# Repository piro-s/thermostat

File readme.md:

# Thermostat:  
A board for connecting an inductive load (the width of the tracks allows you  
to connect up to 5A); if large currents are required, then a connector is  
provided for connecting control signals of an external relay (Relay Control).  
Scheme was made using the [article](https://habr.com/ru/companies/unwds/articles/390601/).  

### Schemes:  
###### thermostat_v0.1:  
[pdf](docs/thermostat_v0.1.pdf)  

### Images:  
###### thermostat_v0.1:  
top:  
  
bottom:  
  
assembly:  

###### gerber:  
Archive for production:  
[thermostat_v0.1](https://github.com/piro-s/thermostat/raw/main/gerber/thermostat_v0.1.zip)

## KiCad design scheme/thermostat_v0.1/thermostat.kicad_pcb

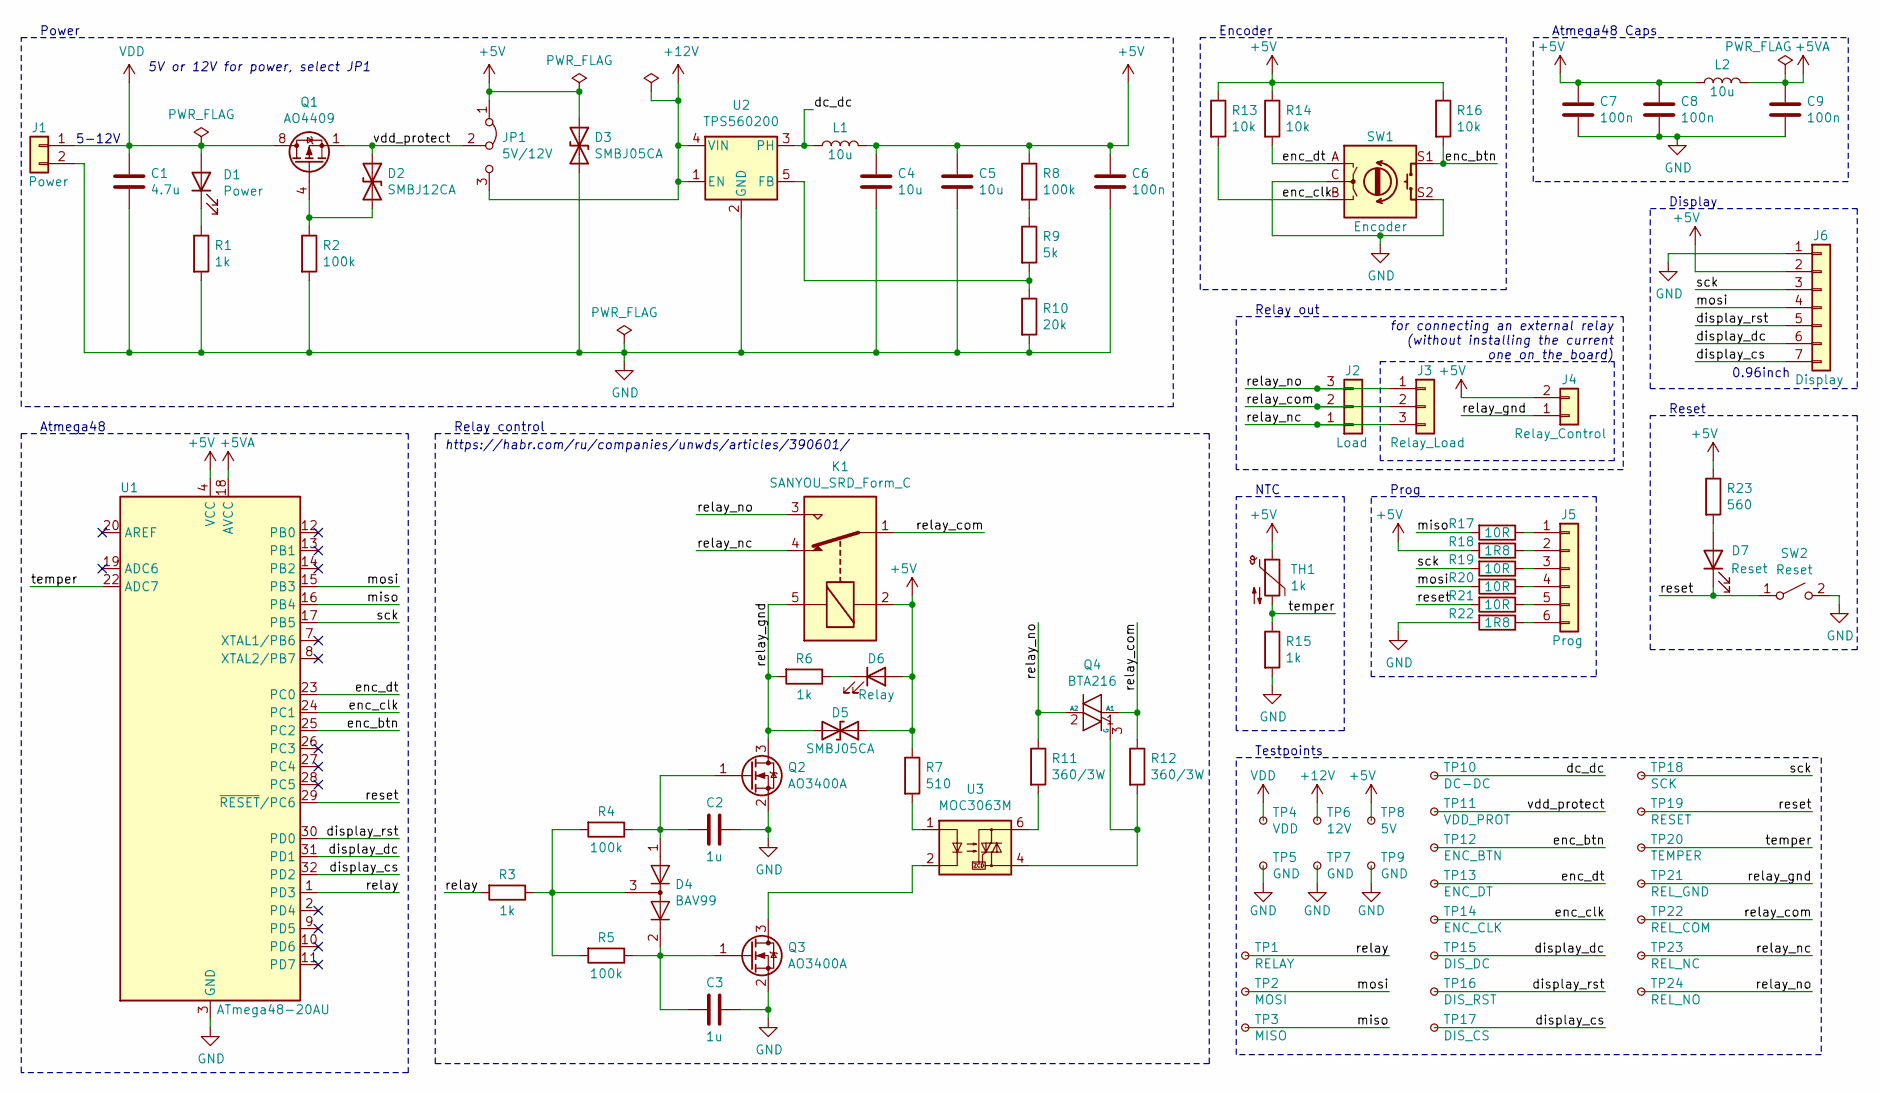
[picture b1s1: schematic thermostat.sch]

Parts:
C1: 4.7u; C_1206_3216Metric_Pad1.33x1.80mm_HandSolder
C2, C3: 1u; C_0603_1608Metric_Pad1.08x0.95mm_HandSolder
C4, C5: 10u; C_1206_3216Metric_Pad1.33x1.80mm_HandSolder
C6, C7, C8, C9: 100n; C_0603_1608Metric_Pad1.08x0.95mm_HandSolder
D1: Power; D_0603_1608Metric_Pad1.05x0.95mm_HandSolder
D2: SMBJ12CA; D_SMA_Handsoldering
D3, D5: SMBJ05CA; D_SMA_Handsoldering
D4: BAV99; SOT-23
D6: Relay; D_0603_1608Metric_Pad1.05x0.95mm_HandSolder
D7: Reset; D_0603_1608Metric_Pad1.05x0.95mm_HandSolder
J1: Power; PhoenixContact_MCV_1,5_2-G-5.08_1x02_P5.08mm_Vertical
J2: Load; PhoenixContact_MCV_1,5_3-G-5.08_1x03_P5.08mm_Vertical
J3: Relay_Load; SolderWire-0.75sqmm_1x03_P4.8mm_D1.25mm_OD2.3mm
J4: Relay_Control; PhoenixContact_MCV_1,5_2-G-5.08_1x02_P5.08mm_Vertical
J5: Prog; IDC-Header_2x03_P2.54mm_Vertical
J6: Display; Display_WAVGAT_0.96
JP1: 5V/12V; PinHeader_1x03_P2.54mm_Vertical
K1: SANYOU_SRD_Form_C; Relay_SPDT_SANYOU_SRD_Series_Form_C
L1, L2: 10u; L_0805_2012Metric_Pad1.15x1.40mm_HandSolder
Q1: AO4409; SOIC-8_3.9x4.9mm_P1.27mm
Q2, Q3: AO3400A; SOT-23
Q4: BTA216; TO-220-3_Vertical
R1, R3, R6, R15: 1k; R_0603_1608Metric_Pad0.98x0.95mm_HandSolder
R2, R4, R5, R8: 100k; R_0603_1608Metric_Pad0.98x0.95mm_HandSolder
R7: 510; R_0603_1608Metric_Pad0.98x0.95mm_HandSolder
R9: 5k; R_0603_1608Metric_Pad0.98x0.95mm_HandSolder
R10: 20k; R_0603_1608Metric_Pad0.98x0.95mm_HandSolder
R11, R12: 360/3W; R_Axial_DIN0617_L17.0mm_D6.0mm_P20.32mm_Horizontal
R13, R14, R16: 10k; R_0603_1608Metric_Pad0.98x0.95mm_HandSolder
R17, R19, R20, R21: 10R; R_0603_1608Metric_Pad0.98x0.95mm_HandSolder
R18, R22: 1R8; R_0603_1608Metric_Pad0.98x0.95mm_HandSolder
R23: 560; R_0603_1608Metric_Pad0.98x0.95mm_HandSolder
SW1: Encoder; RotaryEncoder_Alps_EC11E-Switch_Vertical_H20mm
SW2: Reset; SW_PUSH_6mm
TH1: 1k; PinSocket_1x02_P1.27mm_Vertical
TP1: RELAY; TestPoint_THTPad_D1.0mm_Drill0.5mm
TP2: MOSI; TestPoint_THTPad_D1.0mm_Drill0.5mm
TP3: MISO; TestPoint_THTPad_D1.0mm_Drill0.5mm
TP4: VDD; TestPoint_THTPad_D1.0mm_Drill0.5mm
TP5, TP7, TP9: GND; TestPoint_THTPad_D1.0mm_Drill0.5mm
TP6: 12V; TestPoint_THTPad_D1.0mm_Drill0.5mm
TP8: 5V; TestPoint_THTPad_D1.0mm_Drill0.5mm
TP10: DC-DC; TestPoint_THTPad_D1.0mm_Drill0.5mm
TP11: VDD_PROT; TestPoint_THTPad_D1.0mm_Drill0.5mm
TP12: ENC_BTN; TestPoint_THTPad_D1.0mm_Drill0.5mm
TP13: ENC_DT; TestPoint_THTPad_D1.0mm_Drill0.5mm
TP14: ENC_CLK; TestPoint_THTPad_D1.0mm_Drill0.5mm
TP15: DIS_DC; TestPoint_THTPad_D1.0mm_Drill0.5mm
TP16: DIS_RST; TestPoint_THTPad_D1.0mm_Drill0.5mm
TP17: DIS_CS; TestPoint_THTPad_D1.0mm_Drill0.5mm
TP18: SCK; TestPoint_THTPad_D1.0mm_Drill0.5mm
TP19: RESET; TestPoint_THTPad_D1.0mm_Drill0.5mm
TP20: TEMPER; TestPoint_THTPad_D1.0mm_Drill0.5mm
TP21: REL_GND; TestPoint_THTPad_D1.0mm_Drill0.5mm
TP22: REL_COM; TestPoint_THTPad_D1.0mm_Drill0.5mm
TP23: REL_NC; TestPoint_THTPad_D1.0mm_Drill0.5mm
TP24: REL_NO; TestPoint_THTPad_D1.0mm_Drill0.5mm
U1: ATmega48-20AU; TQFP-32_7x7mm_P0.8mm
U2: TPS560200; SOT-23-5
U3: MOC3063M; DIP-6_W7.62mm

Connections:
+5V: C4.1, C5.1, C6.1, C7.1, C8.1, D3.1 (A1), D5.1 (A1), D6.2 (A), J4.2, J6.2, JP1.1 (A), K1.2, L1.2, L2.1, R7.1, R8.1, R13.1, R14.1, R16.1, R18.2, R23.1, TH1.1, TP8.1, U1.4 (VCC), U1.6 (VCC)
+5VA: C9.1, L2.2, U1.18 (AVCC)
+12V: JP1.3 (B), TP6.1, U2.1 (EN), U2.4 (VIN)
/dc_dc: L1.1, TP10.1, U2.3 (PH)
/display_cs: J6.7, TP17.1, U1.32 (PD2)
/display_dc: J6.6, TP15.1, U1.31 (PD1)
/display_rst: J6.5, TP16.1, U1.30 (PD0)
/enc_btn: R16.2, SW1.S1, TP12.1, U1.25 (PC2)
/enc_clk: R13.2, SW1.B, TP14.1, U1.24 (PC1)
/enc_dt: R14.2, SW1.A, TP13.1, U1.23 (PC0)
/miso: R17.2, TP3.1, U1.16 (PB4)
/mosi: J6.4, R20.2, TP2.1, U1.15 (PB3)
/relay: R3.2, TP1.1, U1.1 (PD3)
/relay_com: J2.2, J3.2, K1.1, Q4.1 (A1), R12.1, TP22.1
/relay_gnd: D5.2 (A2), J4.1, K1.5, Q2.3 (D), R6.2, TP21.1
/relay_nc: J2.1, J3.3, K1.4, TP23.1
/relay_no: J2.3, J3.1, K1.3, Q4.2 (A2), R11.1, TP24.1
/reset: D7.1 (K), R21.2, SW2.1 (A), TP19.1, U1.29 (~RESET~/PC6)
/sck: J6.3, R19.2, TP18.1, U1.17 (PB5)
/temper: R15.1, TH1.2, TP20.1, U1.22 (ADC7)
/vdd_protect: D2.1 (A1), JP1.2 (C), Q1.1 (S), Q1.2 (S), Q1.3 (S), TP11.1
GND: C1.2, C2.1, C3.1, C4.2, C5.2, C6.2, C7.2, C8.2, C9.2, D3.2 (A2), J1.2, J6.1, Q2.2 (S), Q3.2 (S), R1.2, R2.2, R10.2, R15.2, R22.2, SW1.C, SW1.S2, SW2.2 (B), TP5.1, TP7.1, TP9.1, U1.3 (GND), U1.5 (GND), U1.21 (GND), U2.2 (GND)
unnamed: C2.2, D4.1 (K), Q2.1 (G), R4.1
unnamed: C3.2, D4.2 (A), Q3.1 (G), R5.1
unnamed: D1.1 (K), R1.1
unnamed: D2.2 (A2), Q1.4 (G), R2.1
unnamed: D4.3 (K), R3.1, R4.2, R5.2
unnamed: D6.1 (K), R6.1
unnamed: D7.2 (A), R23.2
unnamed: J5.1, R17.1
unnamed: J5.2, R18.1
unnamed: J5.3, R19.1
unnamed: J5.4, R20.1
unnamed: J5.5, R21.1
unnamed: J5.6, R22.1
unnamed: Q3.3 (D), U3.2
unnamed: Q4.3 (G), R12.2, U3.4
unnamed: R7.2, U3.1
unnamed: R8.2, R9.1
unnamed: R9.2, R10.1, U2.5 (FB)
unnamed: R11.2, U3.6
VDD: C1.1, D1.2 (A), J1.1, Q1.5 (D), Q1.6 (D), Q1.7 (D), Q1.8 (D), TP4.1

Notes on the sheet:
Power
Atmega48 Caps
NTC
Encoder
for connecting an external relay (without installing the current one on the board)
Relay out
Relay control
https://habr.com/ru/companies/unwds/articles/390601/
5-12V
Reset
Prog
0.96inch
Display
Atmega48
Testpoints
5V or 12V for power, select JP1

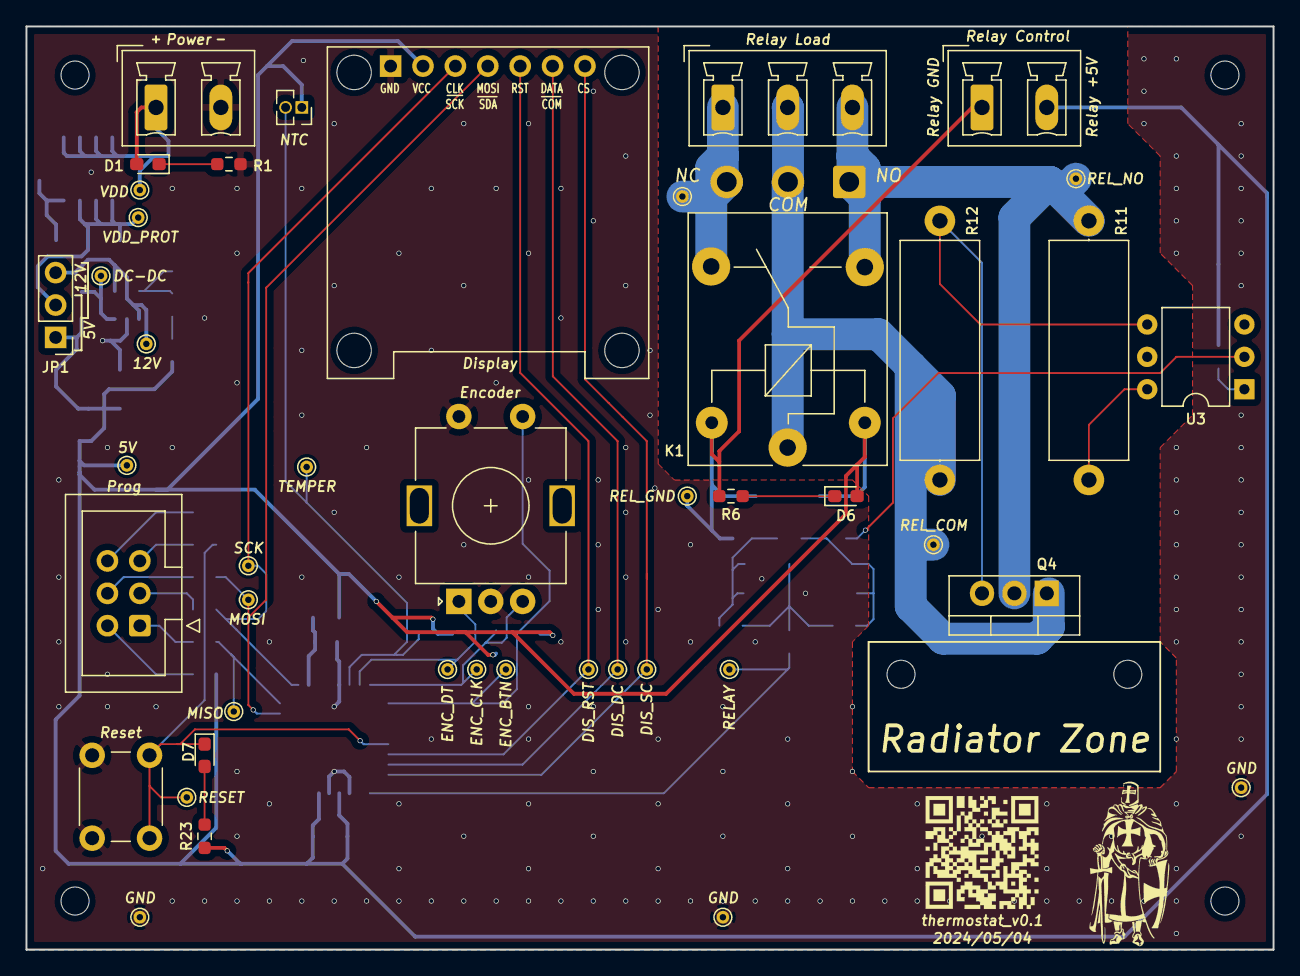
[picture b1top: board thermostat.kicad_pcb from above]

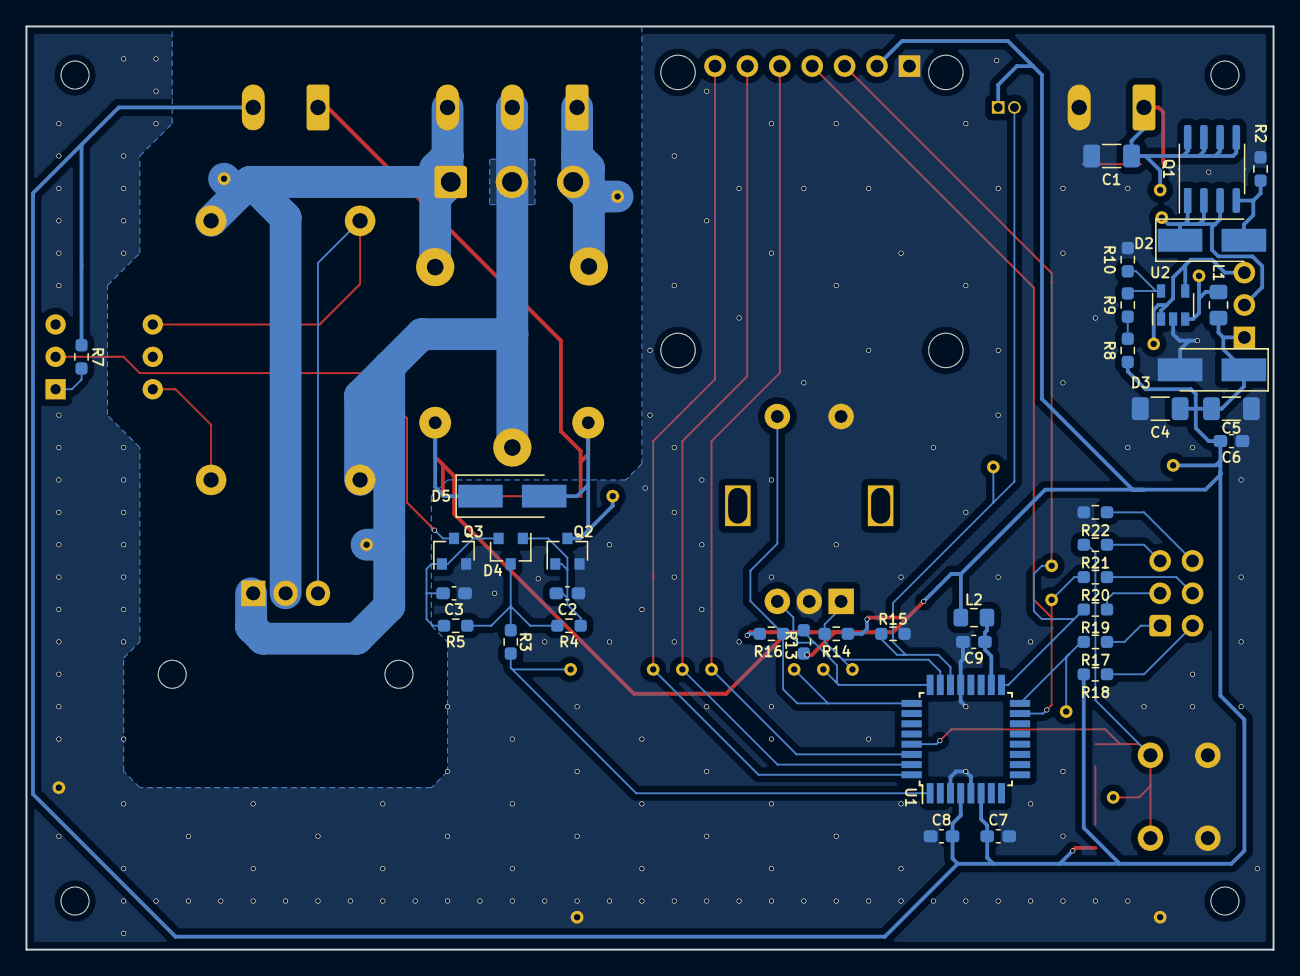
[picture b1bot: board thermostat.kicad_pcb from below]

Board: 2 copper layers, 97.8 x 72.4 mm, 83 parts (38 on the bottom side), 42 nets.

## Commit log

2024-05-04 Initial
